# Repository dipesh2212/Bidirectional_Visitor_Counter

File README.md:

# Bidirectional_Visitor_Counter
PROBLEM STATEMENT: 

Design a credit card-sized counter device (images attached below for reference) that can keep a count on the occupancy of an indoor venue. The device is ideally mounted at the entrance of the room. The device has sensors to detect when a person enters or exits the room and can distinguish whether someone is ‘Entering’ or ‘Exiting’. The green and red circles indicated in the image below are indicative positions of the sensors. It has a 2-digit 7-segment display to show the count. As a guest enters the device detects and the count on the display increments by 1 with every guest entering. Similarly while exiting the guests the device detects and the count on the display decrements by 1. The simple solution helps inform guests about the occupancy and they can choose not to enter if the occupancy is near or above the spatial capacity of the venue. You’re tasked with designing the electronics for this device wherein you have to design a single 2-layered PCB that hosts all the electronic components needed. 

Working of the project:

The system is designed for optimum energy usage and is very beneficial in case if we want to count the number of people going to attend a particular event or any function thereby helps in collecting data by counting the number of people. This is done by simply incrementing the counter.
The system uses InfraRed Sensor pairs in order to fulfil this purpose and thus saves a large amount of energy. Each pair consists of 2 sensor pairs placed at a certain distance from one another in the opposite direction. The IR transmitter is used to transmit IR rays straight to the receiver which receives the input and feeds this to an 8051 Microcontroller.
As soon as a person enters the area where the system is placed, it is detected by the IR sensor module and this info is fed to the microcontroller. The microcontroller process this input received. At this time the system also counts the number of people present and increments a counter on each arrival, this count is displayed on a 7 segment display.
Summary

Microcontroller:

I have tried to design the PCB in Eagle Software. 
The main hardware I have used for the task is Arduino Nano. The reason behind using Nano is the that it has operating voltage of 5 V which is mentioned in the assignment. Apart from this the microcontroller which is Microchip ATmega328P is capable controller with flash memory if 32 KB which is more than sufficient for trivial tasks. 

Looking at the technical specifications of the Nano board, we find the following features:
 
o	ATmega328P Microcontroller is from the 8-bit AVR family
o	The operating voltage is 5V
o	Input voltage (Vin) is 7V to 12V
o	Input/Output Pins are 22
o	EEPROM is 1 KB
o	CLK speed is 16 MHz
o	Weight-7g
o	The size of the printed circuit board is 18 X 45mm
o	Supports three communications like SPI, IIC, & USART
o	Flash memory is 32 KB
o	SRAM is 2 KB
o	Analog i/p pins are 6 from A0 to A5
o	Digital pins are 14
o	Power consumption is 19 mA
o	I/O pins DC Current is 40 mA

IR Sensors

Tsop sensor: The tsop1738 is a infrared receiver tuned to react only to ir of frequency 38 khz. This ir sensor module consists of a pin diode and a pre amplifier which are embedded into a single package. The output of tsop is active low and it gives +5v in off state.

Display
7 segment display used is DS1 with 2 units of 74HC595 shift resisters for two wat 7 segment displays

Power Supply

The Arduino Uno can be powered via the USB connection or with an external power
supply. The power source is selected automatically. External (non-USB) power can come either
from an AC-to-DC adapter (wall-wart) or battery. The adapter can be connected by plugging a
2.1mm centre-positive plug into the board's power jack. Leads from a battery can be inserted in the
Gnd and Vin pin headers of the POWER connector.
The board can operate on an external supply of 6 to 20 volts. If supplied with less than 7V,
however, the 5V pin may supply less than five volts and the board may be unstable. If using more
than I2V, the voltage regulator may overheat and damage the board. The recommended range 1S /
to 12 volts

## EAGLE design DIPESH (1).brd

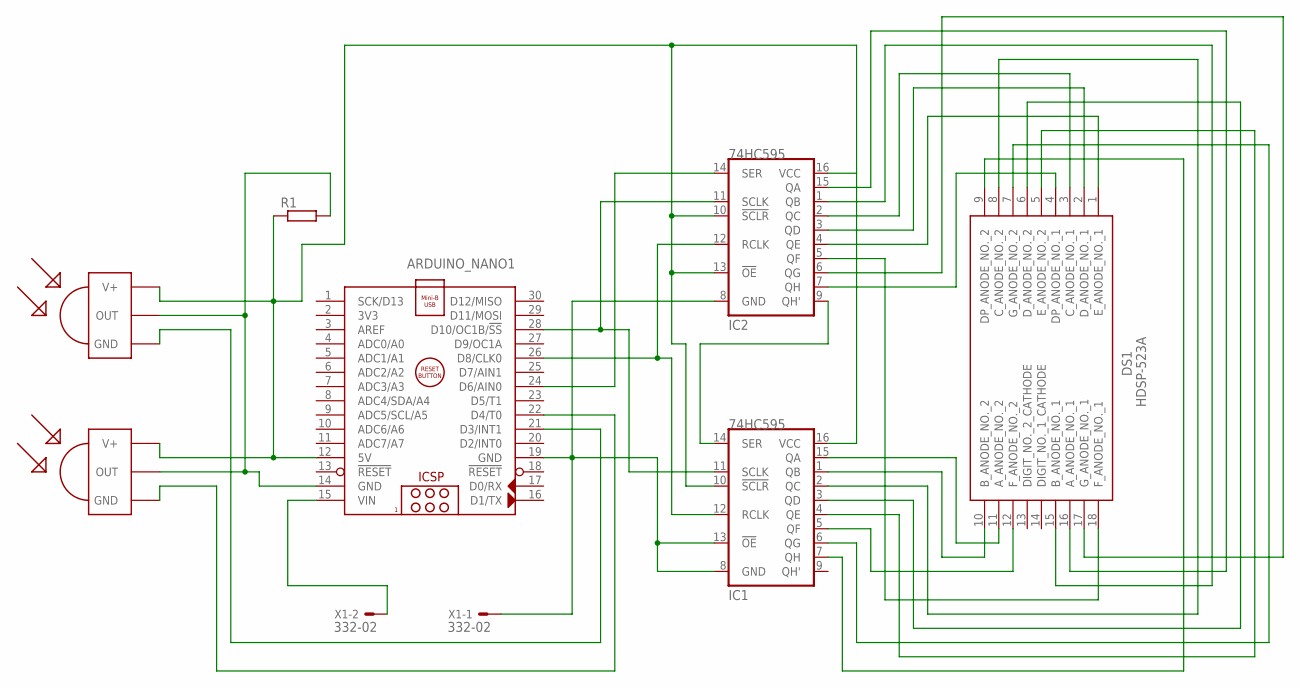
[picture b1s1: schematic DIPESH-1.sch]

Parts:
ARDUINO_NANO1: ARDUINO_NANO
DS1: HDSP-523A; DIPS1524W50P254L2500H800Q18N
IC1, IC2: 74HC595; SO16
R1: R-EU_0207/10; 0207/10
TSOP1, TSOP2: TSOP1730; TSOP17XX
X1: 332-02

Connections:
unnamed: ARDUINO_NANO1.19 (GND), IC1.8 (GND), IC1.13 (!OE), IC2.8 (GND), X1.1
unnamed: ARDUINO_NANO1.21 (D3/INT1), TSOP1.GND
unnamed: ARDUINO_NANO1.22 (D4/T0), TSOP2.GND
unnamed: IC1.14 (SER), IC2.9 (QH')
unnamed: ARDUINO_NANO1.15 (VIN), X1.2
unnamed: ARDUINO_NANO1.12 (5V), IC1.10 (!SCLR), IC1.16 (VCC), IC2.10 (!SCLR), IC2.13 (!OE), IC2.16 (VCC), R1.1, TSOP1.V+, TSOP2.V+
unnamed: ARDUINO_NANO1.14 (GND), R1.2, TSOP1.OUT, TSOP2.OUT
unnamed: DS1.11 (A_ANODE_NO._2), IC1.15 (QA)
unnamed: ARDUINO_NANO1.24 (D6/AIN0), IC2.14 (SER)
unnamed: DS1.16 (A_ANODE_NO._1), IC2.15 (QA)
unnamed: ARDUINO_NANO1.26 (D8/CLK0), IC1.12 (RCLK), IC2.12 (RCLK)
unnamed: ARDUINO_NANO1.28 (D10/OC1B/!SS), IC1.11 (SCLK), IC2.11 (SCLK)
unnamed: DS1.15 (B_ANODE_NO._1), IC2.1 (QB)
unnamed: DS1.5 (E_ANODE_NO._2), IC1.4 (QE)
unnamed: DS1.10 (B_ANODE_NO._2), IC1.1 (QB)
unnamed: DS1.8 (C_ANODE_NO._2), IC1.2 (QC)
unnamed: DS1.3 (C_ANODE_NO._1), IC2.2 (QC)
unnamed: DS1.2 (D_ANODE_NO._1), IC2.3 (QD)
unnamed: DS1.6 (D_ANODE_NO._2), IC1.3 (QD)
unnamed: DS1.1 (E_ANODE_NO._1), IC2.4 (QE)
unnamed: DS1.18 (F_ANODE_NO._1), IC2.5 (QF)
unnamed: DS1.12 (F_ANODE_NO._2), IC1.5 (QF)
unnamed: DS1.7 (G_ANODE_NO._2), IC1.6 (QG)
unnamed: DS1.17 (G_ANODE_NO._1), IC2.6 (QG)
unnamed: DS1.9 (DP_ANODE_NO._2), IC1.7 (QH)
unnamed: DS1.4 (DP_ANODE_NO._1), IC2.7 (QH)

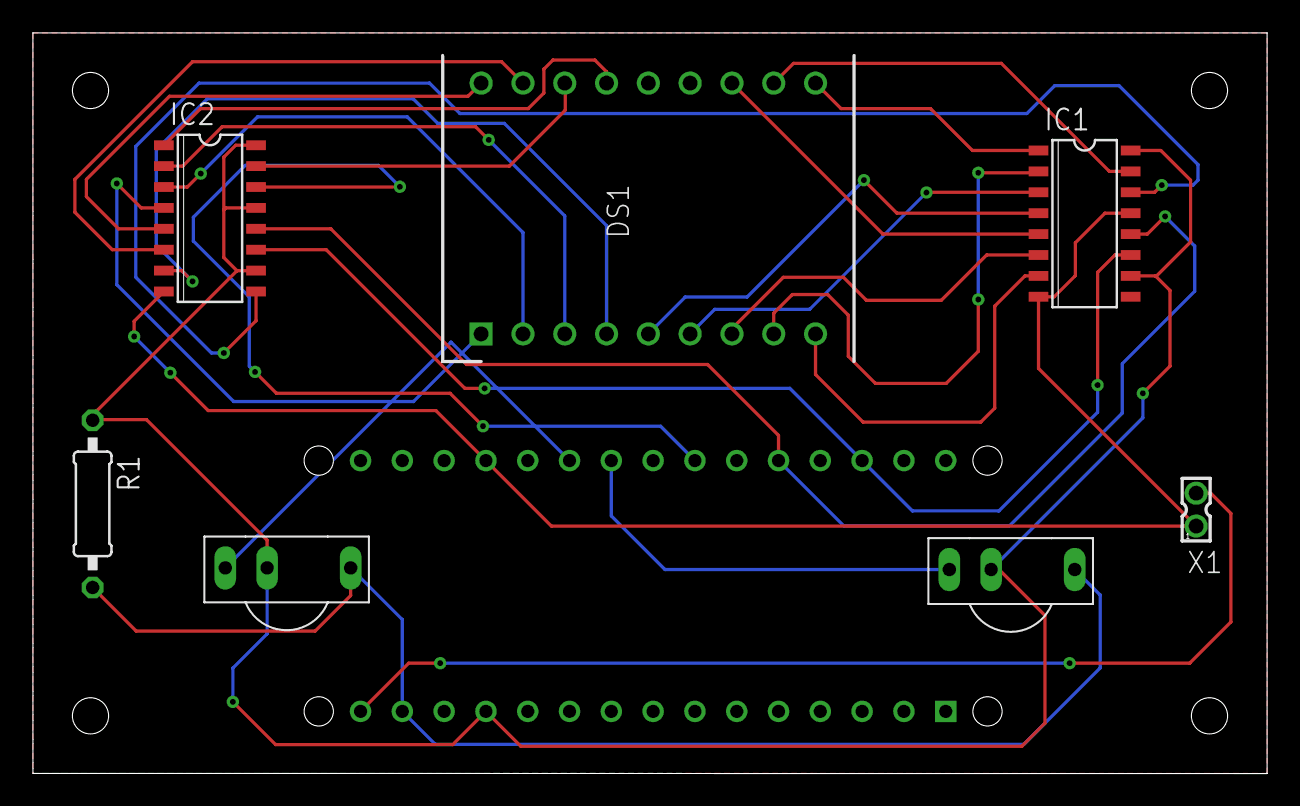
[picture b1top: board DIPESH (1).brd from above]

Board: 2 copper layers, 75.0 x 45.0 mm, 8 parts (1 on the bottom side), 26 nets.

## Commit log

2023-02-07 Project commit
